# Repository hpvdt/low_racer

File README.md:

# Lowracer Project

This was a project run in the 2020-21 academic year to build a lowracer for ASME based on the work done for Zephyr (2018-19) and Blueshift (2019-20). However due to the COVID-19 pandemic running *(much)* longer than expected the lowracer's construction made no meaningful progress during the year due to lockdowns and was ultimately cancelled to focus on the aircraft project that was being started in 2021.

The boards were designed, ordered, and assembled. However no code was prepared since the project was cancelled shortly after the boards were assembled.

## Software Used

The board designs were originally done in KiCad 5, but have been ported forward to 7.0.10. **This was the team's first project to use KiCad over EAGLE!**

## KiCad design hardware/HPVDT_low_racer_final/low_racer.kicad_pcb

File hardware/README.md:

# Hardware Designs

For this project there were two students which were designing different boards based off a schematic they developed together. They were Rishabh Iyer and Kartikey Sachdeva.

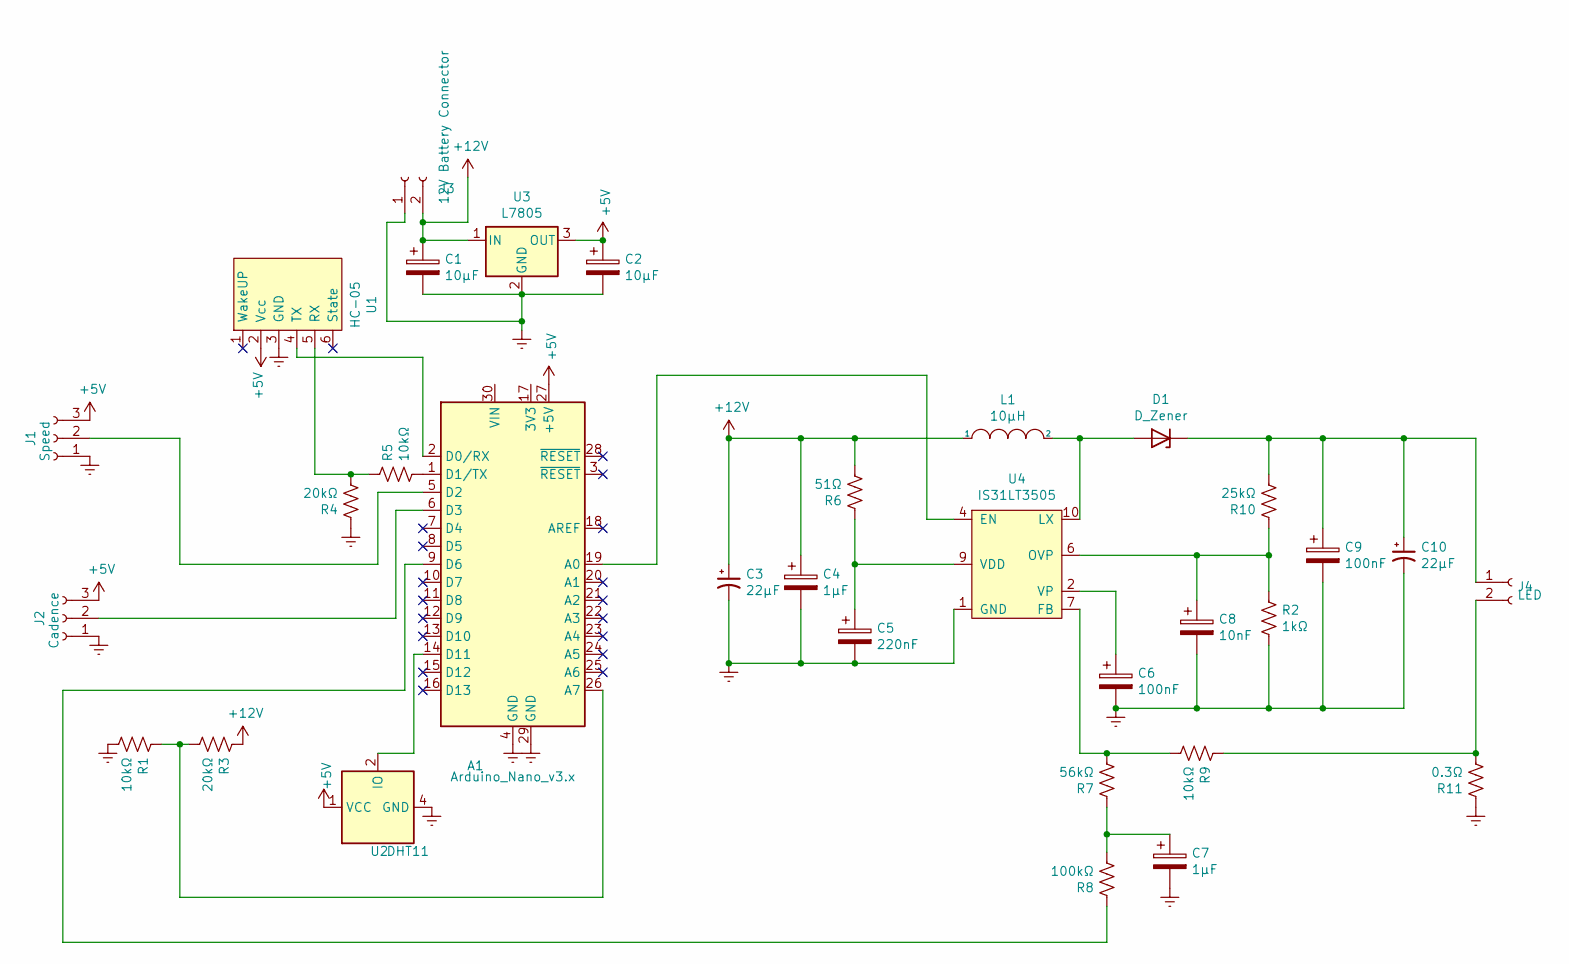
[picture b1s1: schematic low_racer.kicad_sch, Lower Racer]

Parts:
A1: Arduino_Nano_v3.x; Arduino_Nano
C1, C2: 10μF; C_0603_1608Metric
C3, C10: 22μF; C_0805_2012Metric
C4, C7: 1μF; C_0603_1608Metric
C5: 220nF; C_0603_1608Metric
C6, C9: 100nF; C_0603_1608Metric
C8: 10nF; C_0603_1608Metric
D1: D_Zener; D_PowerDI-123
J1: Speed; PinSocket_1x03_P2.54mm_Vertical
J2: Cadence; PinSocket_1x03_P2.54mm_Vertical
J3: 12V Battery Connector; PinSocket_1x02_P2.54mm_Vertical
J4: LED; PinSocket_1x02_P2.54mm_Vertical
L1: 10μH; L_Taiyo-Yuden_MD-5050
R1, R5, R9: 10kΩ; R_0603_1608Metric
R2: 1kΩ; R_0603_1608Metric
R3, R4: 20kΩ; R_0603_1608Metric
R6: 51Ω; R_0603_1608Metric
R7: 56kΩ; R_0603_1608Metric
R8: 100kΩ; R_0603_1608Metric
R10: 25kΩ; R_0603_1608Metric
R11: 0.3Ω; R_0805_2012Metric
U1: HC-05
U2: DHT11; Aosong_DHT11_5.5x12.0_P2.54mm
U3: L7805; TO-220-3_Horizontal_TabDown
U4: IS31LT3505; MSOP-10-1EP_3x3mm_P0.5mm_EP1.73x1.98mm_ThermalVias

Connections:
+5V: A1.27 (+5V), C2.1, J1.3, J2.3, U1.2 (Vcc), U2.1 (VCC), U3.3 (OUT)
+12V: C1.1, C3.1, C4.1, J3.2, L1.1, R3.1, R6.2, U3.1 (IN)
Earth: A1.4 (GND), A1.29 (GND), C1.2, C2.2, C3.2, C4.2, C5.2, C6.2, C7.2, C8.2, C9.2, C10.2, J1.1, J2.1, J3.1, R1.2, R2.2, R4.1, R11.1, U1.3 (GND), U2.4 (GND), U3.2 (GND), U4.1 (GND), U4.3 (GND), U4.5 (GND), U4.11 (GND)
unnamed: A1.1 (D1/TX), R5.2
unnamed: A1.2 (D0/RX), U1.4 (TX)
unnamed: A1.5 (D2), J1.2
unnamed: A1.6 (D3), J2.2
unnamed: A1.9 (D6), R8.1
unnamed: A1.14 (D11), U2.2 (IO)
unnamed: A1.19 (A0), U4.4 (EN)
unnamed: A1.26 (A7), R1.1, R3.2
unnamed: C5.1, R6.1, U4.9 (VDD)
unnamed: C6.1, U4.2 (VP)
unnamed: C7.1, R7.1, R8.2
unnamed: C8.1, R2.1, R10.1, U4.6 (OVP)
unnamed: C9.1, C10.1, D1.1 (K), J4.1, R10.2
unnamed: D1.2 (A), L1.2, U4.10 (LX)
unnamed: J4.2, R9.1, R11.2
unnamed: R4.2, R5.1, U1.5 (RX)
unnamed: R7.2, R9.2, U4.7 (FB)

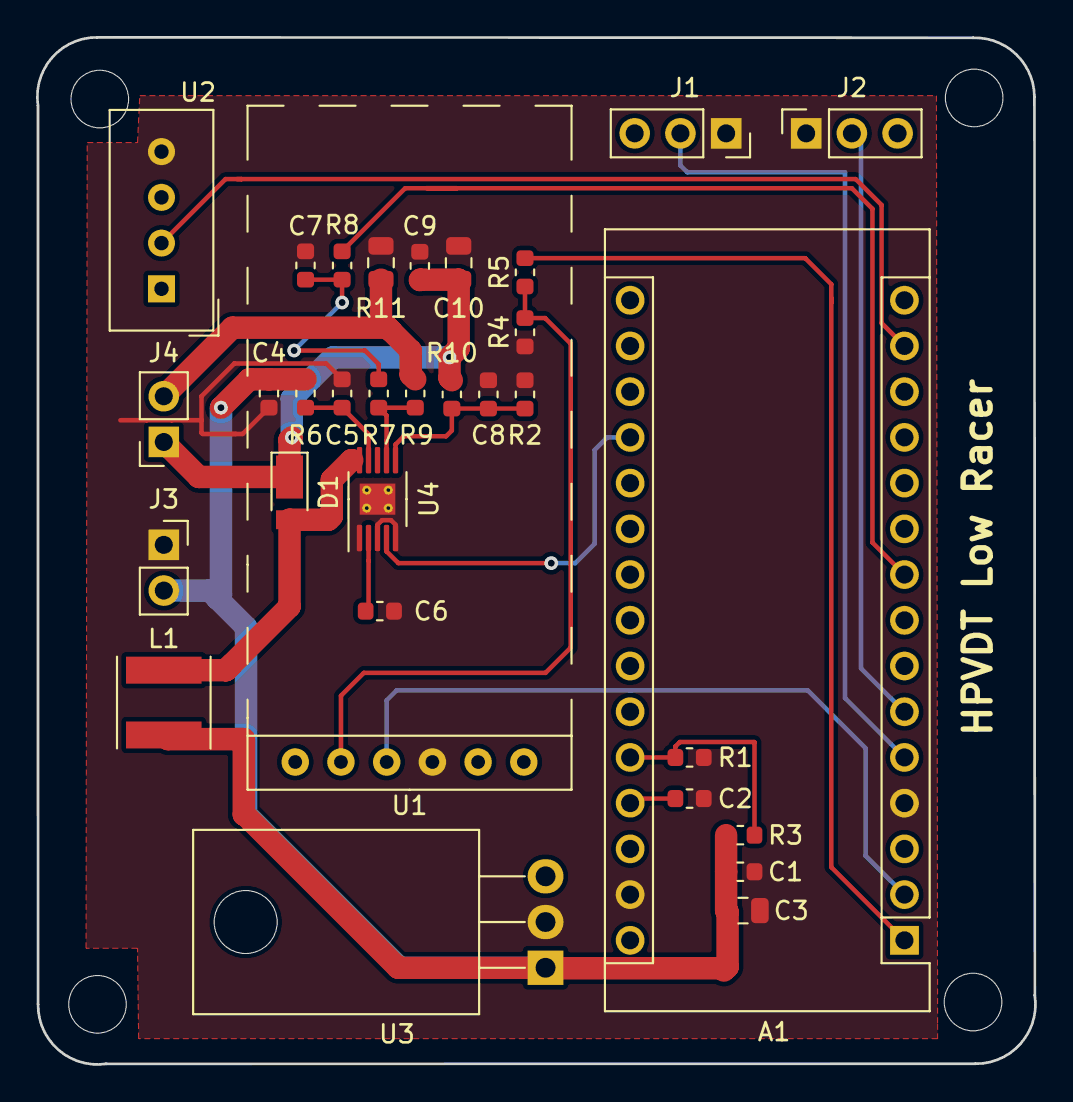
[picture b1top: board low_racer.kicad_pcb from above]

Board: 2 copper layers, 55.5 x 57.1 mm, 32 parts (0 on the bottom side), 20 nets.

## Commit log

2024-01-04 Uploaded hardware files
2024-01-04 Added licence
